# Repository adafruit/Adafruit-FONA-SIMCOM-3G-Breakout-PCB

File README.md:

## Adafruit FONA SIMCOM 3G Breakouts PCB
<a href="http://www.adafruit.com/products/3147"><br/>
Click here to purchase one from the Adafruit shop</a>

For those who want to take it to the next level we now have a 3G Cellular Modem breakout! The FONA 3G has better coverage, GSM backwards-compatibility and even sports a built-in GPS module for geolocation & asset tracking. This all-in-one cellular phone module with that lets you add location-tracking, voice, text, SMS and data to your project in a single breakout.

This module measure only 1.75"x1.6" but packs a surprising amount of technology into it's little frame. At the heart is a powerfull GSM cellular module (we use the latest SIM5320A) with integrated GPS.

For more details, see the various versions available:

  * https://www.adafruit.com/products/3147
  * https://www.adafruit.com/products/2687
  * https://www.adafruit.com/products/2691
  * https://www.adafruit.com/products/2696
  
PCB files for the Adafruit FONA SIMCOM 3G Breakout. The format is EagleCAD schematic and board layout

### License

Adafruit invests time and resources providing this open source design, please support Adafruit and open-source hardware by purchasing products from [Adafruit](https://www.adafruit.com)!

All text above must be included in any redistribution

Designed by Limor Fried/Ladyada for Adafruit Industries.
Creative Commons Attribution/Share-Alike, all text above must be included in any redistribution. 
See license.txt for additional information.

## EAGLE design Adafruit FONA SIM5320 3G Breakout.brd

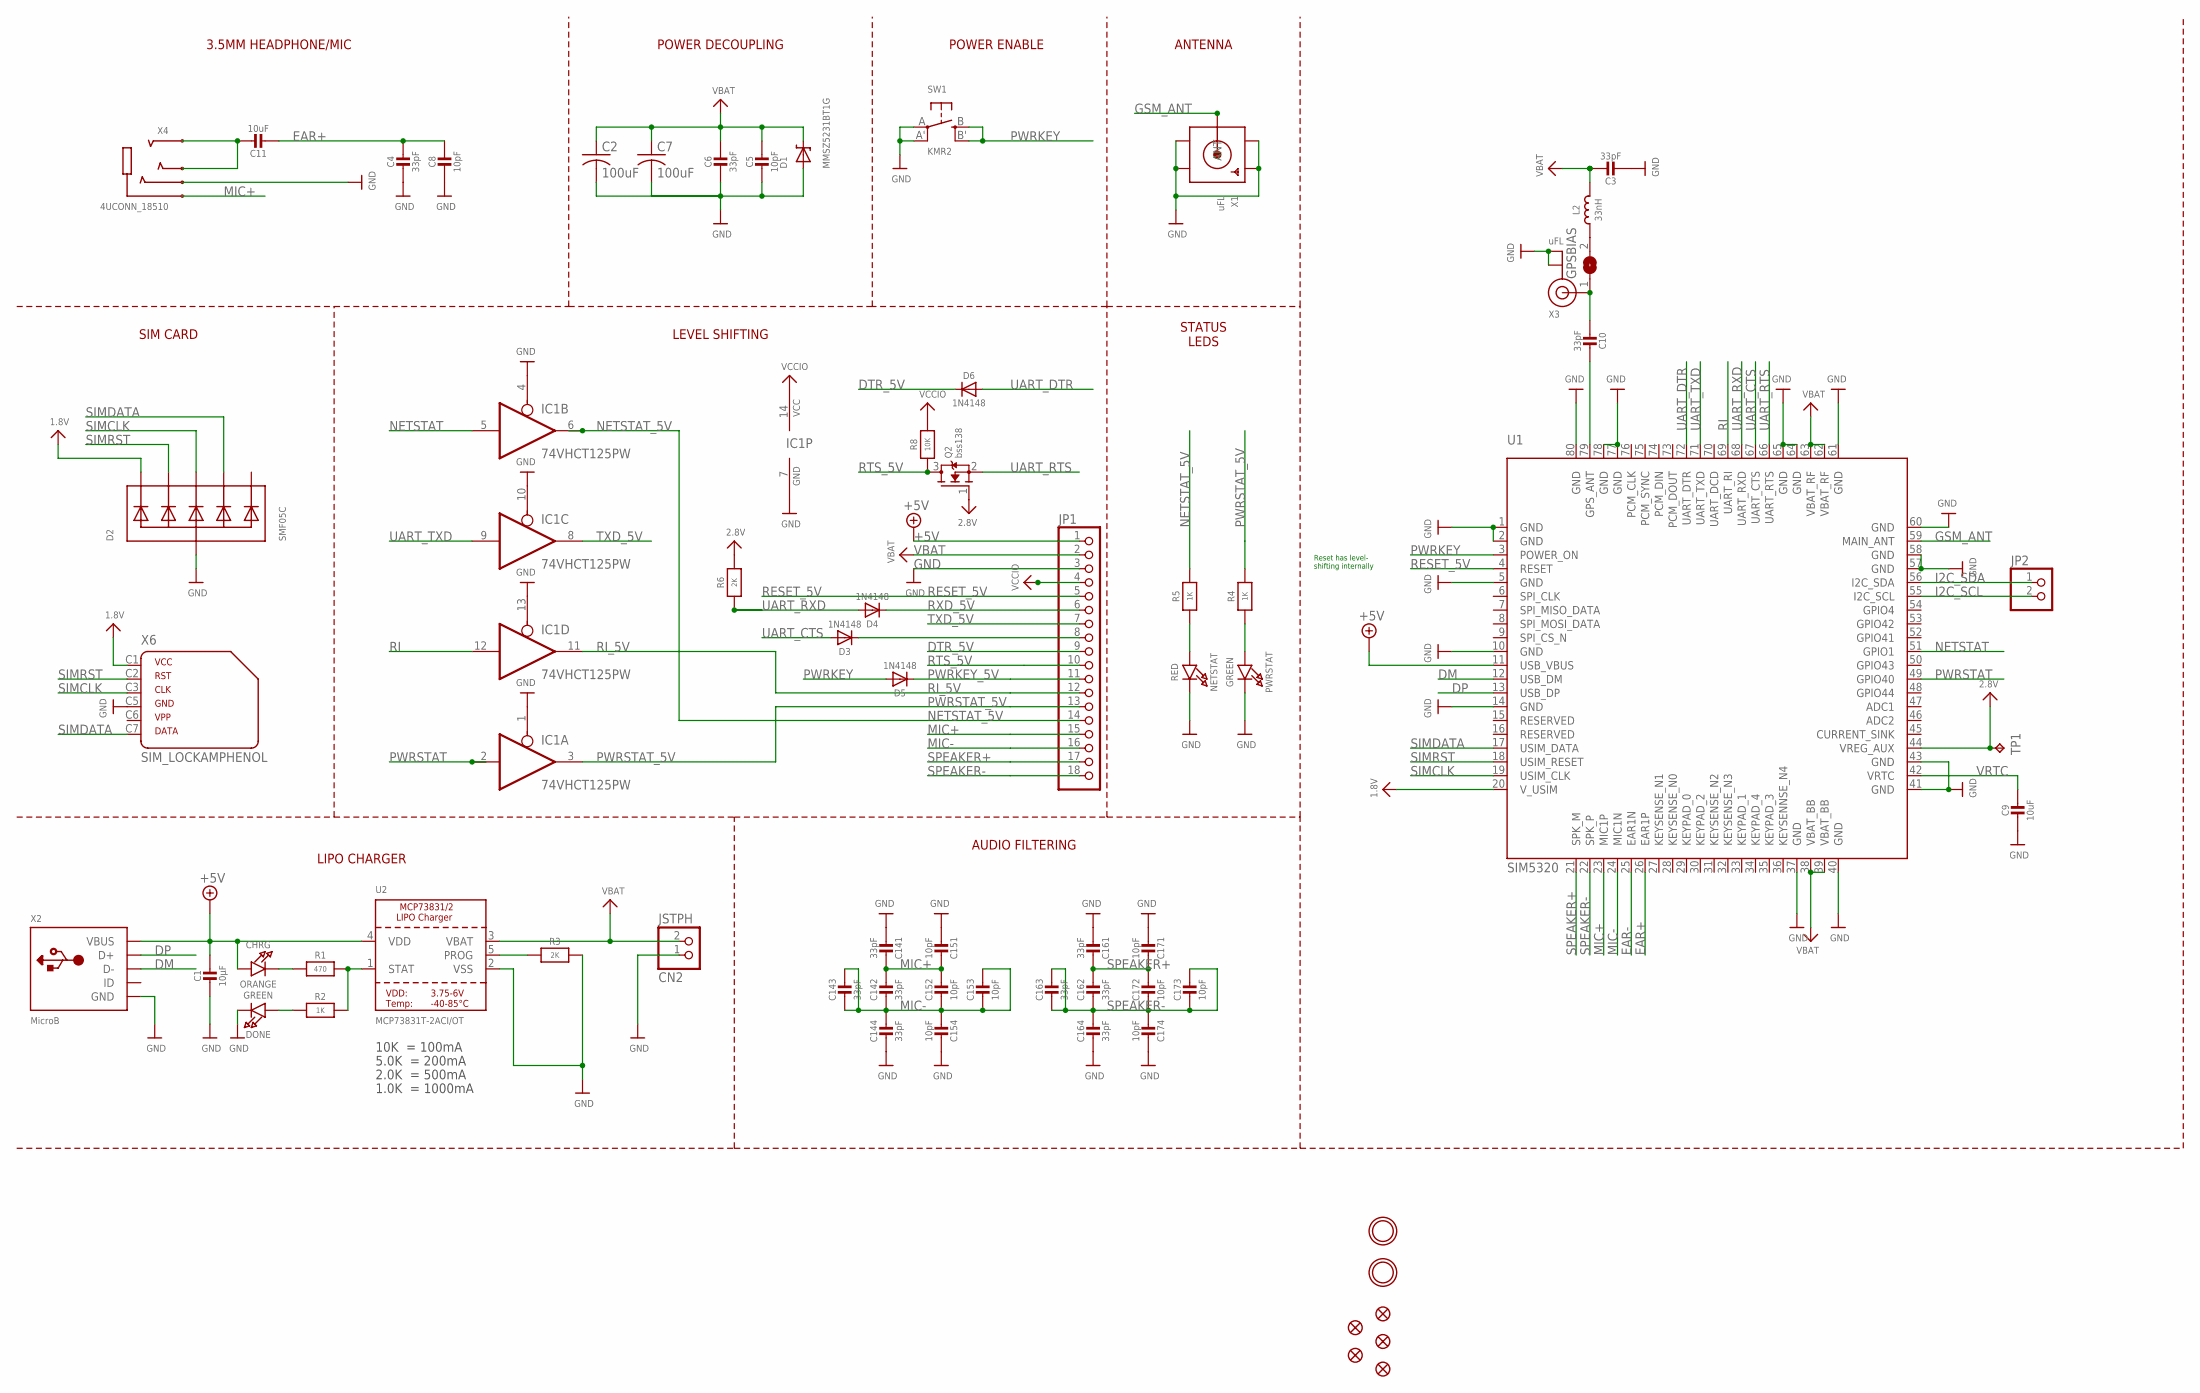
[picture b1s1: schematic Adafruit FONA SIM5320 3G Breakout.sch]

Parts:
C1: 10µF; 0805-NO
C2, C7: 100uF; C1210
C3, C4, C6, C10: 33pF; 0805-NO
C5, C8: 10pF; 0805-NO
C9, C11: 10uF; 0805-NO
C14, C16: 33pF; RESPACK_4X0603
C15, C17: 10pF; RESPACK_4X0603
CHRG: ORANGE; CHIPLED_0805_NOOUTLINE
CN2: JSTPH; JSTPH2
D1: MMSZ5231BT1G; SOD-123
D2: SMF05C; SOT363
D3, D4, D5, D6: 1N4148; SOD-323
DONE: GREEN; CHIPLED_0805_NOOUTLINE
FID1, FID2, FID3, FID4, FID5: FIDUCIAL""; FIDUCIAL_1MM
GPSBIAS: SOLDERJUMPER; SOLDERJUMPER_ARROW_NOPASTE
IC1: 74VHCT125PW; TSSOP14
JP1: HEADER-1X18; 1X18_ROUND70
JP2: HEADER-1X2ROUND; 1X02_ROUND
L2: 33nH; _0805MP
NETSTAT: RED; CHIPLED_0805_NOOUTLINE
PWRSTAT: GREEN; CHIPLED_0805_NOOUTLINE
Q2: bss138; SOT23-WIDE
R1: 470; 0805-NO
R2, R4, R5: 1K; 0805-NO
R3, R6: 2K; 0805-NO
R8: 10K; 0805-NO
SW1: KMR2; BTN_KMR2_4.6X2.8
TP1: TPTP11R; TP11R
U1: SIM5320
U2: MCP73831T-2ACI/OT; SOT23-5
U$33, U$34: MOUNTINGHOLE2.5; MOUNTINGHOLE_2.5_PLATED
X1: uFL; SMA_EDGELAUNCH_UFL
X2: MicroB; 4UCONN_20329
X3: uFL; U.FL
X4: 4UCONN_18510
X6: SIM_LOCKAMPHENOL; C707_10M006_512_2

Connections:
1.8V: D2.1 (C1), U1.20 (V_USIM), X6.C1 (1)
2.8V: Q2.1 (G), R6.2, TP1.TP, U1.44 (VREG_AUX)
+5V: C1.1, CHRG.A, JP1.1, U1.11 (USB_VBUS), U2.4 (VDD), X2.VBUS
CTS_5V: D3.C, JP1.8
DM: U1.12 (USB_DM), X2.D-
DP: U1.13 (USB_DP), X2.D+
DTR_5V: D6.C, JP1.9
EAR+: C4.1, C8.1, C11.2, U1.26 (EAR1P)
EAR-: U1.25 (EAR1N)
GND: C1.2, C2.2, C3.2, C4.2, C5.2, C6.2, C7.2, C8.2, C9.2, C14.5 (2), C14.8 (2), C15.4 (1), C15.8 (2), C16.5 (2), C16.8 (2), C17.4 (1), C17.8 (2), CN2.1, D1.A, D2.2 (A), DONE.C, IC1.1 (OE), IC1.4 (OE), IC1.7 (GND), IC1.10 (OE), IC1.13 (OE), JP1.3, NETSTAT.C, PWRSTAT.C, R3.2, SW1.A, SW1.A' (P1), U1.1 (GND), U1.2 (GND), U1.5 (GND), U1.10 (GND), U1.14 (GND), U1.37 (GND), U1.40 (GND), U1.41 (GND), U1.43 (GND), U1.57 (GND), U1.58 (GND), U1.60 (GND), U1.61 (GND), U1.64 (GND), U1.65 (GND), U1.77 (GND), U1.78 (GND), U1.80 (GND), U2.2 (VSS), X1.GND@1 (GND1), X1.GND@2 (GND2), X1.GND@3 (GND3), X1.GND@4 (GND4), X2.BASE@1 (GND), X2.BASE@2 (GND), X2.GND, X2.SPRT@1 (GND), X2.SPRT@2 (GND), X2.SPRT@3 (GND), X2.SPRT@4 (GND), X3.1 (GND), X3.2 (GND), X4.4-INNER_SLEEVE (RING1), X6.C5 (4)
GSM_ANT: U1.59 (MAIN_ANT), X1.P (ANT)
HP+: C11.1, X4.2-TIP (RING3), X4.3-OUTER_SLEEVE (RING2)
I2C_SCL: JP2.2, U1.55 (I2C_SCL)
I2C_SDA: JP2.1, U1.56 (I2C_SDA)
MIC+: C14.1, C14.2 (1), C15.1, C15.2 (1), JP1.15, U1.23 (MIC1P), X4.1-GND (TIP)
MIC-: C14.3 (1), C14.4 (1), C14.6 (2), C14.7 (2), C15.3 (1), C15.5 (2), C15.6 (2), C15.7 (2), JP1.16, U1.24 (MIC1N)
unnamed: CHRG.C, R1.1
unnamed: R1.2, R2.2, U2.1 (STAT)
unnamed: C10.2, GPSBIAS.1, X3.3 (SIGNAL)
unnamed: PWRSTAT.A, R4.1
unnamed: R3.1, U2.5 (PROG)
unnamed: DONE.A, R2.1
unnamed: C10.1, U1.79 (GPS_ANT)
unnamed: NETSTAT.A, R5.1
unnamed: GPSBIAS.2, L2.1
NETSTAT: IC1.5 (I), U1.51 (GPIO1)
NETSTAT_5V: IC1.6 (O), JP1.14, R5.2
PWRKEY: D5.A, SW1.B (S), SW1.B' (S1), U1.3 (POWER_ON)
PWRKEY_5V: D5.C, JP1.11
PWRSTAT: IC1.2 (I), U1.49 (GPIO40)
PWRSTAT_5V: IC1.3 (O), JP1.13, R4.2
RESET_5V: JP1.5, U1.4 (RESET)
RI: IC1.12 (I), U1.69 (UART_RI)
RI_5V: IC1.11 (O), JP1.12
RTS_5V: JP1.10, Q2.3 (D), R8.1
RXD_5V: D4.C, JP1.6
SIMCLK: D2.4 (C3), U1.19 (USIM_CLK), X6.C3 (3)
SIMDATA: D2.5 (C4), U1.17 (USIM_DATA), X6.C7 (6)
SIMRST: D2.3 (C2), U1.18 (USIM_RESET), X6.C2 (2)
SPEAKER+: C16.1, C16.2 (1), C17.1, C17.2 (1), JP1.17, U1.21 (SPK_M)
SPEAKER-: C16.3 (1), C16.4 (1), C16.6 (2), C16.7 (2), C17.3 (1), C17.5 (2), C17.6 (2), C17.7 (2), JP1.18, U1.22 (SPK_P)
TXD_5V: IC1.8 (O), JP1.7
UART_CTS: D3.A, U1.67 (UART_CTS)
UART_DTR: D6.A, U1.72 (UART_DTR)
UART_RTS: Q2.2 (S), U1.66 (UART_RTS)
UART_RXD: D4.A, R6.1, U1.68 (UART_RXD)
UART_TXD: IC1.9 (I), U1.71 (UART_TXD)
VBAT: C2.1, C3.1, C5.1, C6.1, C7.1, CN2.2, D1.C, JP1.2, L2.2, U1.38 (VBAT_BB), U1.39 (VBAT_BB), U1.62 (VBAT_RF), U1.63 (VBAT_RF), U2.3 (VBAT)
VCCIO: IC1.14 (VCC), JP1.4, R8.2
VRTC: C9.1, U1.42 (VRTC)

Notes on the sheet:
10K = 100mA
5.0K = 200mA
2.0K = 500mA
1.0K = 1000mA
ANTENNA
POWER DECOUPLING
3.5MM HEADPHONE/MIC
SIM CARD
LEVEL SHIFTING
LIPO CHARGER
AUDIO FILTERING
STATUS LEDS
POWER ENABLE
Reset has level- shifting internally

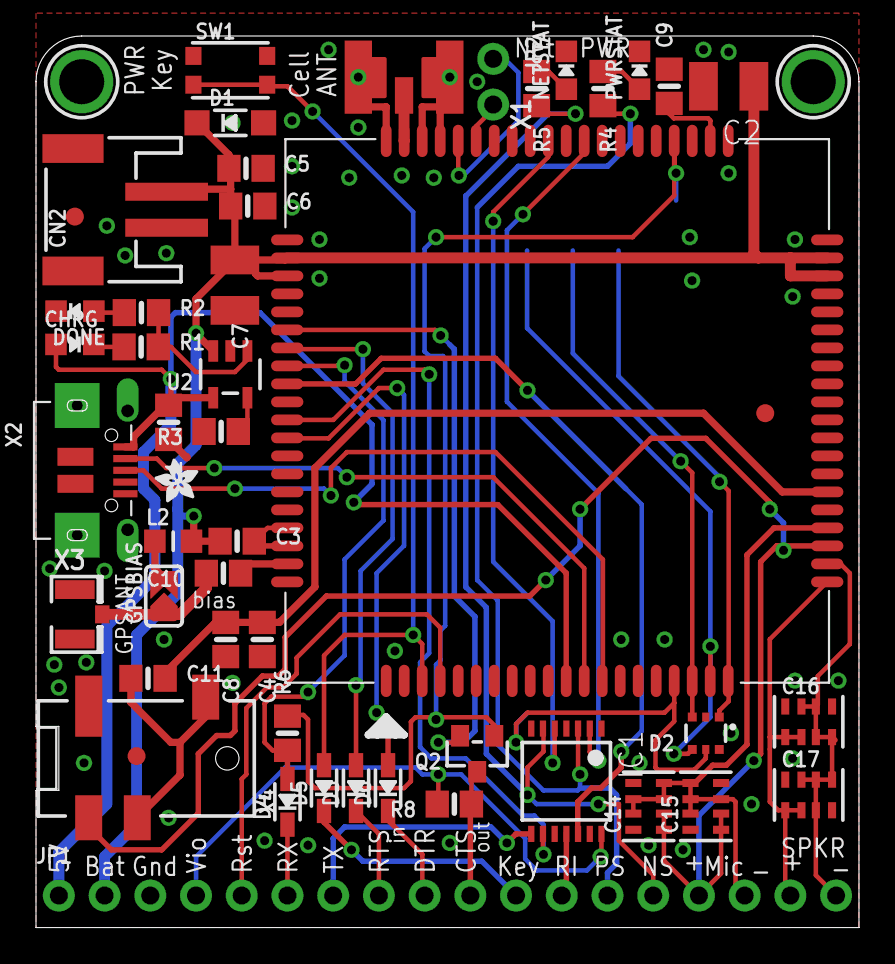
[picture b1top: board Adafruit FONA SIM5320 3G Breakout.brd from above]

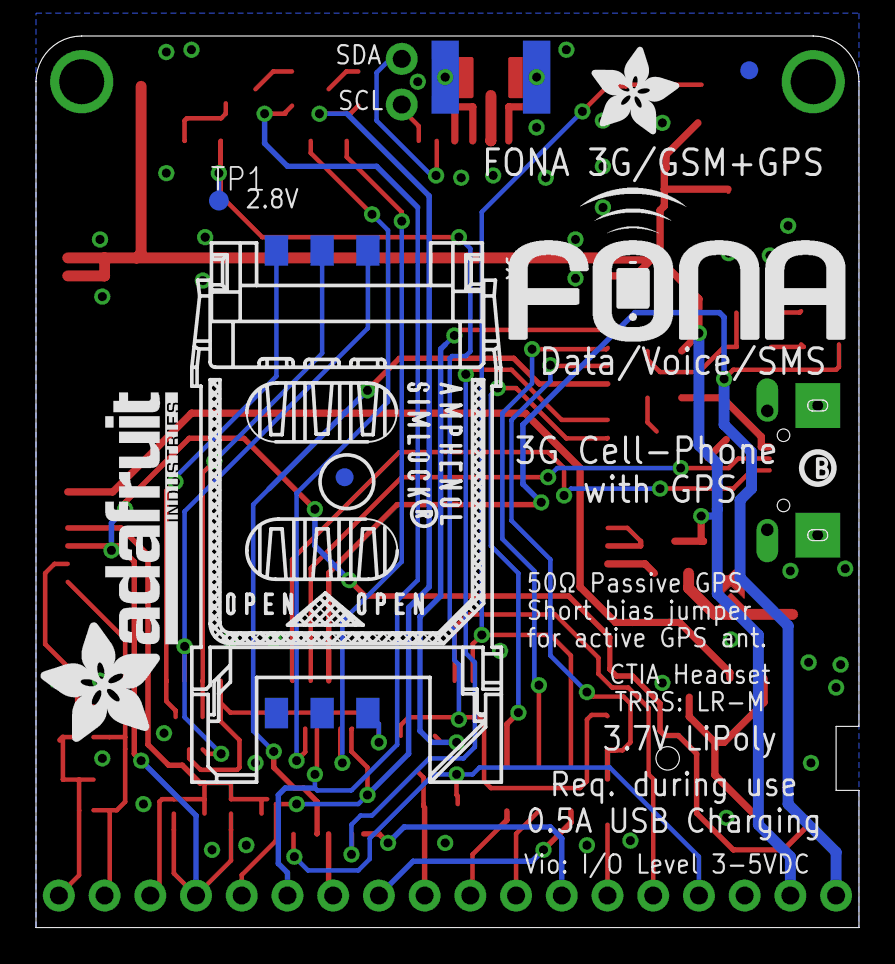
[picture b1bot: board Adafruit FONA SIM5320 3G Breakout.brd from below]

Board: 2 copper layers, 45.7 x 49.5 mm, 60 parts (8 on the bottom side), 49 nets.

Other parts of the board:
U$21: ADAFRUIT_2.5MM
U$25: PCBFEAT-REV-040
U$26: FONA_LOGO
U$36: ADAFRUIT_5MM
U$42: ADAFRUIT_TEXT_20MM

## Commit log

2016-06-19 init!

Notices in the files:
parts and their libraries:
microbuilder: This work is placed in the public domain, and may be freely used for commercial and non-commercial work with the following conditions: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
